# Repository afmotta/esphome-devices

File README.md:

# esphome-devices

ESPHome firmware, hardware sources and configuration for a three-floor residence's home
automation: CAN-bus wall buttons and room sensors, lighting control, and multi-zone
climate control (radiant floor + fancoil, with ventilation). The whole system is
pre-live — hardware is standardized and the firmware is built, but nothing is
physically deployed yet.

## What's where

A layered monorepo: one shared infrastructure layer, two application systems on top of
it, and the PCB sources for the CAN boards.

| Directory | Layer | What it is | Rules |
|---|---|---|---|
| [`canbus/`](canbus/) | infrastructure | CAN transport: frames, heartbeats, node discovery/health, generated node firmware | [`canbus/CLAUDE.md`](canbus/CLAUDE.md) |
| [`lighting/`](lighting/) | application | Button decode → Home Assistant events, hold automations | [`lighting/CLAUDE.md`](lighting/CLAUDE.md) |
| [`climate/`](climate/) | application | Multi-zone heating/cooling/ventilation controller | [`climate/CLAUDE.md`](climate/CLAUDE.md) |
| [`hardware/`](hardware/) | PCB sources | KiCad projects (generated by script) of the CAN wall node and the CAN bridge | [`hardware/README.md`](hardware/README.md) |
| [`registry/`](registry/) | system of record | Node table, bindings, `map.json` | [`registry/README.md`](registry/README.md) |
| `devices/`, `boards/`, `packages/` | composition | Deployable entry points, board definitions, shared packages | root [`CLAUDE.md`](CLAUDE.md) |
| [`docs/`](docs/) | knowledge base | ADRs, architecture, contracts, live climate docs, `archive/` | [`docs/adr/`](docs/adr/) |

## Maintenance & Support Guide

**[afmotta.github.io/esphome-devices](https://afmotta.github.io/esphome-devices/)** —
the practical guide for keeping this system running: everyday monitoring, diagnosing
common problems, and step-by-step hardware-replacement procedures. Written for
someone who doesn't need to know the codebase — a technician, a family member, or
future-you standing next to a dead piece of hardware having scanned a QR code.
Available in [English](https://afmotta.github.io/esphome-devices/) and
[Italiano](https://afmotta.github.io/esphome-devices/it/).

## For AI assistants / developers

See [CLAUDE.md](CLAUDE.md) for the codebase map, architecture, and conventions, and
[CONTRIBUTING.md](CONTRIBUTING.md) for secrets, logging and the registry workflow.
Verify changes with `bash scripts/verification-battery.sh` (CI runs the same gates).

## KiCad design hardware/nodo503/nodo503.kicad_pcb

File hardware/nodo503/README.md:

# Nodo CAN 503 – ESP32-C6-WROOM-1 (rev C)

Nodo per la domotica CAN del fienile, da montare in scatola 503: un morsetto per 24 V e bus CAN, transceiver TJA1051T/3, 6 ingressi pulsante, porta Qwiic (I²C) e modulo **ESP32-C6-WROOM-1-N8** (LCSC C5366877) con Wi-Fi per ESPHome e aggiornamenti OTA. È pensato per il montaggio completo da JLCPCB, con tutti i componenti su un solo lato.

- **Dimensioni:** 55 × 33,5 mm (entro i 56 × 41 mm della CANBed RP2040), 2 strati, spessore 1,6 mm, rame 1 oz
- **Fissaggio:** 2 fori M2,5 non metallizzati (Ø 2,7 mm) in diagonale, in alto a destra e in basso a sinistra, con il centro a 3 mm dai bordi: interasse **49 × 27,5 mm**. Entro 2,8 mm dal centro di ogni foro non ci sono componenti, piste né via, così la testa della vite (fino a Ø 5 mm) appoggia solo su piano di massa coperto da solder mask. L'angolo dell'antenna (in alto a sinistra) resta senza vite: nel case ci sono due appoggi sotto gli angoli senza vite (vedi [case/README.md](case/README.md)).
- **Progetto:** KiCad 7 (si apre anche in KiCad 8/9)
- **Simbolo e footprint del modulo:** dalla libreria ufficiale [espressif/kicad-libraries](https://github.com/espressif/kicad-libraries), licenza CC-BY-SA 4.0. Il footprint comprende anche l'area dell'antenna senza rame.

> Questa è la scheda `hardware/nodo503/`. Per la panoramica di `hardware/` e per la pipeline condivisa vedi [../README.md](../README.md); la seconda scheda, il **bridge CAN** a due canali, è in [../bridge/README.md](../bridge/README.md).

## Contenuto della cartella

Percorsi relativi a `hardware/nodo503/`.

| Percorso | Cosa contiene |
|---|---|
| `nodo503.kicad_pro / .kicad_sch / .kicad_pcb` | Progetto KiCad 7 completo (si apre con KiCad 7, 8 o 9) |
| `nodo503.kicad_sym`, `nodo503.pretty/` | Simbolo e footprint del modulo ESP32-C6-WROOM-1 (libreria di progetto) |
| `out/gerber_JLCPCB.zip` | Gerber + foratura, da caricare così com'è su JLCPCB |
| `out/BOM.csv`, `CPL_JLCPCB.csv` | Distinta e piazzamento per il montaggio completo (SMD + THT) |
| `out/BOM_SMD.csv`, `CPL_SMD.csv` | Distinta e piazzamento solo SMD |
| `out/nodo503_schema.pdf`, `anteprima_lato_*.png` | Schema elettrico e anteprime rame + serigrafia |
| `jlc_library.json` | Libreria JLCPCB (Basic / Preferred / Extended) di ogni codice LCSC |
| `*.py`, `*.sh` | Script che generano schema, PCB, sbroglio e file di produzione (vedi [../docs/pipeline.md](../docs/pipeline.md)) |
| `firmware/nodo503.yaml` | Firmware ESPHome di bring-up (Wi-Fi, API, OTA, 6 pulsanti) |
| [`case/`](case/README.md) | Involucro stampato in 3D (fondo + coperchio a scatto): generatore `gen_case.py`, STL e anteprima |
| [`../docs/decisioni.md`](../docs/decisioni.md) | Storia del progetto e motivazioni delle scelte |
| [`../docs/pipeline.md`](../docs/pipeline.md) | Come rigenerare tutto, struttura degli script, problemi noti |
| [`../CLAUDE.md`](../CLAUDE.md) | Regole per le sessioni di Claude Code su `hardware/` |
| [`../tools/setup.sh`](../tools/setup.sh) | Installa KiCad 7, Freerouting 1.9.0 e le dipendenze Python |

Per rigenerare i file di produzione dopo una modifica: `sudo hardware/tools/setup.sh` (una volta, dalla radice del repo), poi da questa cartella `./route.sh` se cambiano piazzamento o collegamenti, `./build_pcb.sh` se basta lo sbroglio salvato, e infine `./export.sh`.

## Circuito

- **Ingresso 24 V:** PTC da 0,5 A (F1), diodo B5819W contro l'inversione di polarità (D1, 1 A: basta per il PTC da 0,5 A), TVS SMBJ26CA (D2), elettrolitico da 10 µF 50 V e MLCC da 10 µF 50 V in ingresso.
- **5 V:** MORNSUN K7805-500R3 (U1), switching con pin compatibili 7805. Alimenta il TJA1051.
- **3,3 V:** LDO AP2112K-3.3 (U4, 600 mA). Due diodi B5819W (D3, D5) in "OR" lo alimentano dai 5 V del K7805 oppure dai 5 V del pettine di programmazione: il modulo si programma anche senza i 24 V, e la tensione dell'USB non risale verso il K7805.
- **CAN:** TJA1051T/3 con VIO a 3,3 V (nessun partitore sulle linee logiche), pin S a GND, protezione ESD NUP2105L sulle linee del bus. **Nessuna terminazione da 120 Ω** a bordo: il bus va terminato agli estremi della linea.
- **Microcontrollore:** modulo ESP32-C6-WROOM-1-N8 (flash 8 MB, antenna su PCB), con l'antenna a filo del bordo superiore della scheda. Rete RC su EN (10 kΩ + 1 µF) e pull-up da 10 kΩ su GPIO8, come raccomanda Espressif.
- **Ingressi pulsante:** per ciascuno pull-up da 3,3 kΩ a 3,3 V (circa 1 mA nel contatto chiuso, per tenere puliti i contatti in argento dei pulsanti da rete), resistenza in serie da 1 kΩ e condensatore da 100 nF verso GND (τ ≈ 100 µs). Il pulsante chiude verso GND (logica attiva bassa). Componenti 0402 in tre colonne per lato: pulsanti 1–3 a sinistra del modulo, 4–6 a destra.

## Pinout

| Funzione | GPIO | Pin modulo WROOM |
|---|---|---|
| CAN TXD | GPIO23 | 21 |
| CAN RXD | GPIO22 | 20 |
| Pulsante 1 | GPIO7 | 7 |
| Pulsante 2 | GPIO0 | 8 |
| Pulsante 3 | GPIO1 | 9 |
| Pulsante 4 | GPIO20 | 18 |
| Pulsante 5 | GPIO19 | 17 |
| Pulsante 6 | GPIO18 | 16 |
| Qwiic SDA | GPIO3 | 26 |
| Qwiic SCL | GPIO2 | 27 |
| USB D− / D+ (programmazione) | GPIO12 / GPIO13 | 13 / 14 |
| BOOT (pin 5 di J5) | GPIO9 | 15 |
| Pull-up di boot | GPIO8 | 10 |
| Liberi | GPIO4, 5, 6, 10, 11, 15, 16, 17, 21 | – |

Rispetto alla versione 48 × 44 mm i GPIO di pulsanti, Qwiic e CAN sono cambiati: i pulsanti 1–3 usano i pin del lato sinistro del modulo, i pulsanti 4–6 quelli del lato destro, così le piste non si incrociano. GPIO4, GPIO5, GPIO8, GPIO9 e GPIO15 sono pin di strapping: se in futuro ne usi uno, tieni conto del livello che deve avere all'avvio.

## Connettori

- **J1 BUS:** morsetto estraibile ad angolo a 4 poli, passo 3,5 mm, sul bordo destro. Sulla scheda c'è la presa (Kefa KF2EDGR-3.5-4P), a filo del bordo; i fili vanno nella spina a vite (KF2EDGK-3.5-4P), che si innesta di lato da destra, quindi i fili escono paralleli alla scheda come prima. La spina sporge di circa 1 cm oltre il bordo: lascia lo spazio nel case. Dall'alto in basso: 24V – GND – CAN-H – CAN-L.
- **Catena del bus:** il morsetto del bus è uno solo, quindi il cavo che arriva e quello che riparte verso il nodo successivo vanno nello stesso polo della spina (due fili per polo, meglio con un puntale doppio; la spina accetta fino a 1,5 mm² in tutto). Il collegamento tra i due cavi lo fa la spina stessa: sfilandola stacchi la scheda senza interrompere il bus e l'alimentazione degli altri nodi.
- **J3 e J4 PULSANTI:** due connettori JST PH a 4 poli (passo 2 mm, B4B-PH-K-S verticale) sul bordo inferiore, sotto il modulo. **J3** (a sinistra): pulsanti 1, 2, 3, GND da sinistra. **J4** (a destra): pulsanti 4, 5, 6, GND. I connettori sono ruotati di 180°: il pin 1 (tacca quadrata) è a destra ed è il GND, il pin 4 è il pulsante 1 (o 4). Nella maggior parte dei casi basta J3; J4 serve solo per i nodi con più di 3 pulsanti. Il cavo si innesta dall'alto (fili perpendicolari alla scheda) e si sfila per staccare la scheda. Alto 6 mm, 8 mm con il cavo innestato: il componente più alto della scheda resta il K7805.
- **Cavi dei pulsanti:** un cavo a 4 fili per gruppo, con il connettore JST PHR-4 e i contatti SPH-002T-P0.5S (filo da AWG 30 a AWG 24, cioè fino a 0,2 mm²). Il modo più semplice è comprare cavetti PH 2,0 a 4 poli già crimpati, con fili **AWG 24** lunghi 10–15 cm. Il connettore non si salda: si ordina a parte, come prima la spina. La corrente è di circa 1 mA, quindi la sezione conta solo per la meccanica.
- **Collegamento ai frutti:** i pulsanti Vimar Linea hanno morsetti a vite pensati per fili da rete. Metti un **puntale da 0,25 mm²** su ogni filo (oppure ripiega il filo spelato) perché la vite stringa bene. Il GND di ogni cavo va al comune dei 3 frutti del suo gruppo.
- **Montaggio nella scatola:** il JST PH resta innestato per attrito, senza dente di blocco. Lascia un po' di lasco ai cavi quando spingi i frutti nella 503, ed etichetta i due cavi (1–3 e 4–6): hanno lo stesso connettore e si possono scambiare. Nelle scatole dei pulsanti non ci sono conduttori a 230 V; se un giorno ci fossero, i fili sottili dei cavetti PH (isolamento da 300 V) non andrebbero bene così.
- **J2 Qwiic:** JST SH a 4 pin, passo 1 mm, sul bordo superiore a destra con l'imbocco verso l'alto. GND, 3,3 V, SDA, SCL. **Nessun pull-up I²C sulla scheda:** li forniscono il QwiicBus e le schede dei sensori.
- **J5 PROG:** pettine 1×6 a passo 2,54 mm, orizzontale sul bordo inferiore a destra, da non montare (fori passanti). Pin da sinistra: 5V, D−, D+, GND, BOOT, GND (serigrafati sopra i fori). I pin 1–4 vanno al cavo USB (USB nativo del C6). Un ponticello sui pin 5–6 porta GPIO9 a massa e fa partire il modulo in modalità download.

Nessuna terminazione da 120 Ω sulla scheda: il bus va terminato agli estremi della linea.

## Prima programmazione

1. Collega un cavo USB al pettine J5: rosso al 5V, bianco a D−, verde a D+, nero a GND. Puoi saldare un pettine maschio 1×6, oppure infilarne uno nei fori e tenerlo premuto mentre programmi.
2. Con il flash vuoto il modulo di solito entra da solo in modalità download. Se non succede, o se un firmware difettoso ha bloccato l'USB:
   - metti un ponticello sui pin 5–6 di J5 (BOOT–GND);
   - collega l'USB, oppure accendi la scheda;
   - programma, poi **togli il ponticello**. Se lo lasci, il modulo resta in modalità download a ogni riavvio e il firmware non parte.
3. Programma con ESPHome (o esptool) via USB. Dal flash successivo puoi usare l'OTA via Wi-Fi.

## Da verificare prima dell'ordine

1. **Codici LCSC e magazzino.** Tutti i componenti montati hanno un codice LCSC. Al caricamento della BOM controlla la disponibilità, soprattutto di J2 (vedi sotto).
2. **Rotazioni nel file CPL.** Controllale nell'anteprima di assemblaggio JLCPCB, soprattutto per il modulo U3 (l'antenna deve stare a filo del bordo superiore, sopra l'area senza rame), U2, U4 (ruotato di 180°), J2 (ruotato di 180°, imbocco verso l'alto), J1 (ruotato di 90°, imbocco della spina verso il bordo destro), J3 e J4 (la tacca del connettore deve coincidere con quella del footprint), i diodi e C1.
3. **Via nel pad di massa del modulo.** Il pad di massa sotto il WROOM è una griglia 3×3 con 5 via verso la massa sul retro. Su JLCPCB conviene chiedere che le via siano tappate ("via-in-pad" o "epoxy filled"), così lo stagno non cola nei fori. Se non lo fai, di solito funziona comunque.
4. **Piste sotto il modulo.** La pista +3V3 tra i due lati del modulo e le piste USB verso il pettine di programmazione passano sotto il modulo, lontano dall'antenna (sullo strato superiore e sul retro). È ammesso, ma lascia meno piano di massa sotto il modulo.
5. **Fori di J1.** Il footprint Phoenix MC ha fori da 1,2 mm. Il datasheet Kefa non è consultabile da qui: confronta il diametro con il footprint EasyEDA di C441173 (pagina del componente su LCSC o JLCPCB) prima di ordinare. J3 e J4 usano il footprint KiCad del JST PH originale.

## Montaggio

- **Montaggio completo:** carica `BOM.csv` e `CPL_JLCPCB.csv`. JLCPCB monta anche i THT (K7805-500R3, J1, J3 e J4) a onda o a mano. Non resta nulla da saldare, J5 resta senza componente. La spina KF2EDGK-3.5-4P (J1) e i cavi PH per J3/J4 si ordinano a parte.
- **Solo SMD:** carica `BOM_SMD.csv` e `CPL_SMD.csv`. Il K7805, J1, J3 e J4 restano da saldare a mano.

## Firmware ESPHome

Il file `firmware/nodo503.yaml` è una prima versione per collegare il nodo a Home Assistant: Wi-Fi, API cifrata, OTA, 6 pulsanti (GPIO7/0/1 e 20/19/18) e segnale Wi-Fi. CAN e I²C sono lasciati commentati in fondo al file.

1. Copia `firmware/secrets.yaml.example` in `firmware/secrets.yaml` (ignorato da git) e compila SSID, password e chiavi.
2. Dalla cartella `firmware/` esegui `esphome run nodo503.yaml` (o carica il file nella dashboard ESPHome). Il primo flash è via USB su J5, dopo si può usare l'OTA.
3. Home Assistant scopre il dispositivo da solo (Impostazioni → Dispositivi → ESPHome).

Se J4 non è collegato, i pulsanti 4–6 restano semplicemente spenti.

## Firmware per la rete CAN

Il firmware di produzione non è in questa cartella: il profilo `buttons-c6` del registry usa la scheda [`boards/esp32-c6-nodo503.yaml`](../../boards/esp32-c6-nodo503.yaml) (ADR-0025, vedi [`docs/adr/0025-esp32-c6-node-and-bridge-boards.md`](../../docs/adr/0025-esp32-c6-node-and-bridge-boards.md)); i file dei nodi si generano da `registry/nodes.csv` con `canbus/tools/generate_nodes.py`. Il file `firmware/nodo503.yaml` (vedi sopra) è solo il bring-up Wi-Fi/Home Assistant.

## BOM e librerie JLCPCB (aggiornata il 2026-10-14)

Tutti i componenti hanno un codice LCSC e sono pensati per il montaggio completo da JLCPCB, compresi i THT (J1, J3, J4 e K7805 U1, saldati da JLCPCB a onda o a mano). La colonna **Libreria JLCPCB** della BOM indica Basic / Preferred / Extended; l'elenco usato è in `nodo503/jlc_library.json`.

- **Non montati:** solo **J5** (pettine di programmazione, DNP). Per programmare si usa un pettine inserito al momento o saldato.
- **C2** è passato da 2,2 µF a **10 µF 50 V 1206** (C13585, Basic): più capacità in ingresso al K7805 e un componente Extended in meno.
- **C1:** Honor Elec RVT1H100M0505 (C86603, Extended), 10 µF 50 V, 5 × 5,4 mm, 105 °C. Dalla ricerca risultavano circa 6 000 pezzi su LCSC: verificalo al caricamento della BOM.
- **D1:** B5819W (C8598, Basic), lo stesso diodo di D3 e D5: al posto dello SS34 in SMA.
- **J1:** presa Kefa KF2EDGR-3.5-4P (C441173, Extended, ad angolo, 10 A 300 V, saldatura a onda, PCBA Economic e Standard), footprint Phoenix MC 1,5/4-G-3,5 orizzontale, fronte della presa a filo del bordo destro. A magazzino LCSC 7 295 pezzi il 2026-10-18. Prima dell'ordine verifica nell'anteprima JLCPCB che l'imbocco della spina sia verso il bordo.
- **Spina per J1 da ordinare a parte:** Kefa KF2EDGK-3.5-4P (LCSC C440849, 12 196 pezzi il 2026-10-18), vite M2, filo fino a 1,5 mm².
- **J3 e J4:** JST B4B-PH-K-S(LF)(SN) originale (C131334, Extended, saldatura a onda), lo stesso codice per i due connettori. Dalla ricerca del 2026-10-19 risultavano circa 95 000 pezzi su LCSC: verificalo al caricamento della BOM.
- **Cavi per J3/J4 da ordinare a parte:** cavetti PH 2,0 a 4 poli già crimpati (fili AWG 24), oppure connettori JST PHR-4 con contatti SPH-002T-P0.5S da crimpare. Non sono nella BOM di montaggio perché non si saldano.
- **CPL:** per i THT la posizione è il centro dei pin (non il pin 1). Controlla nell'anteprima di assemblaggio le rotazioni dei morsetti e del K7805.
- **J2 (C160404) ha pochissimi pezzi a magazzino.** Alternative compatibili Qwiic (Extended, da confrontare con il footprint): ZX-SH1.0-4PWT C7430446, HC-1.0-4PWT C2845363, BX-SH1.0-4PWT C18077910.
- Le pagine JLCPCB dei componenti Preferred mostrano solo "Extended": al caricamento della BOM verifica che abbiano il badge "Preferred".

## Storia e decisioni

Esiste anche una variante con un unico morsetto estraibile Kefa a 7 poli per i pulsanti (scheda 55 × 37 mm, spina a vite e cordina da 0,5 mm²): è nel branch `variante/kefa` del repo archiviato `afmotta/can-bus-node`, con i suoi file di produzione. Non è stata importata in questo monorepo.

La storia del progetto (rev A con XIAO, rev B con MINI-1, revisione di un esperto, passaggio a 56 × 41 mm e poi a 55 × 33,5 mm, scelta dei connettori) e il motivo di ogni scelta sono in [../docs/decisioni.md](../docs/decisioni.md).

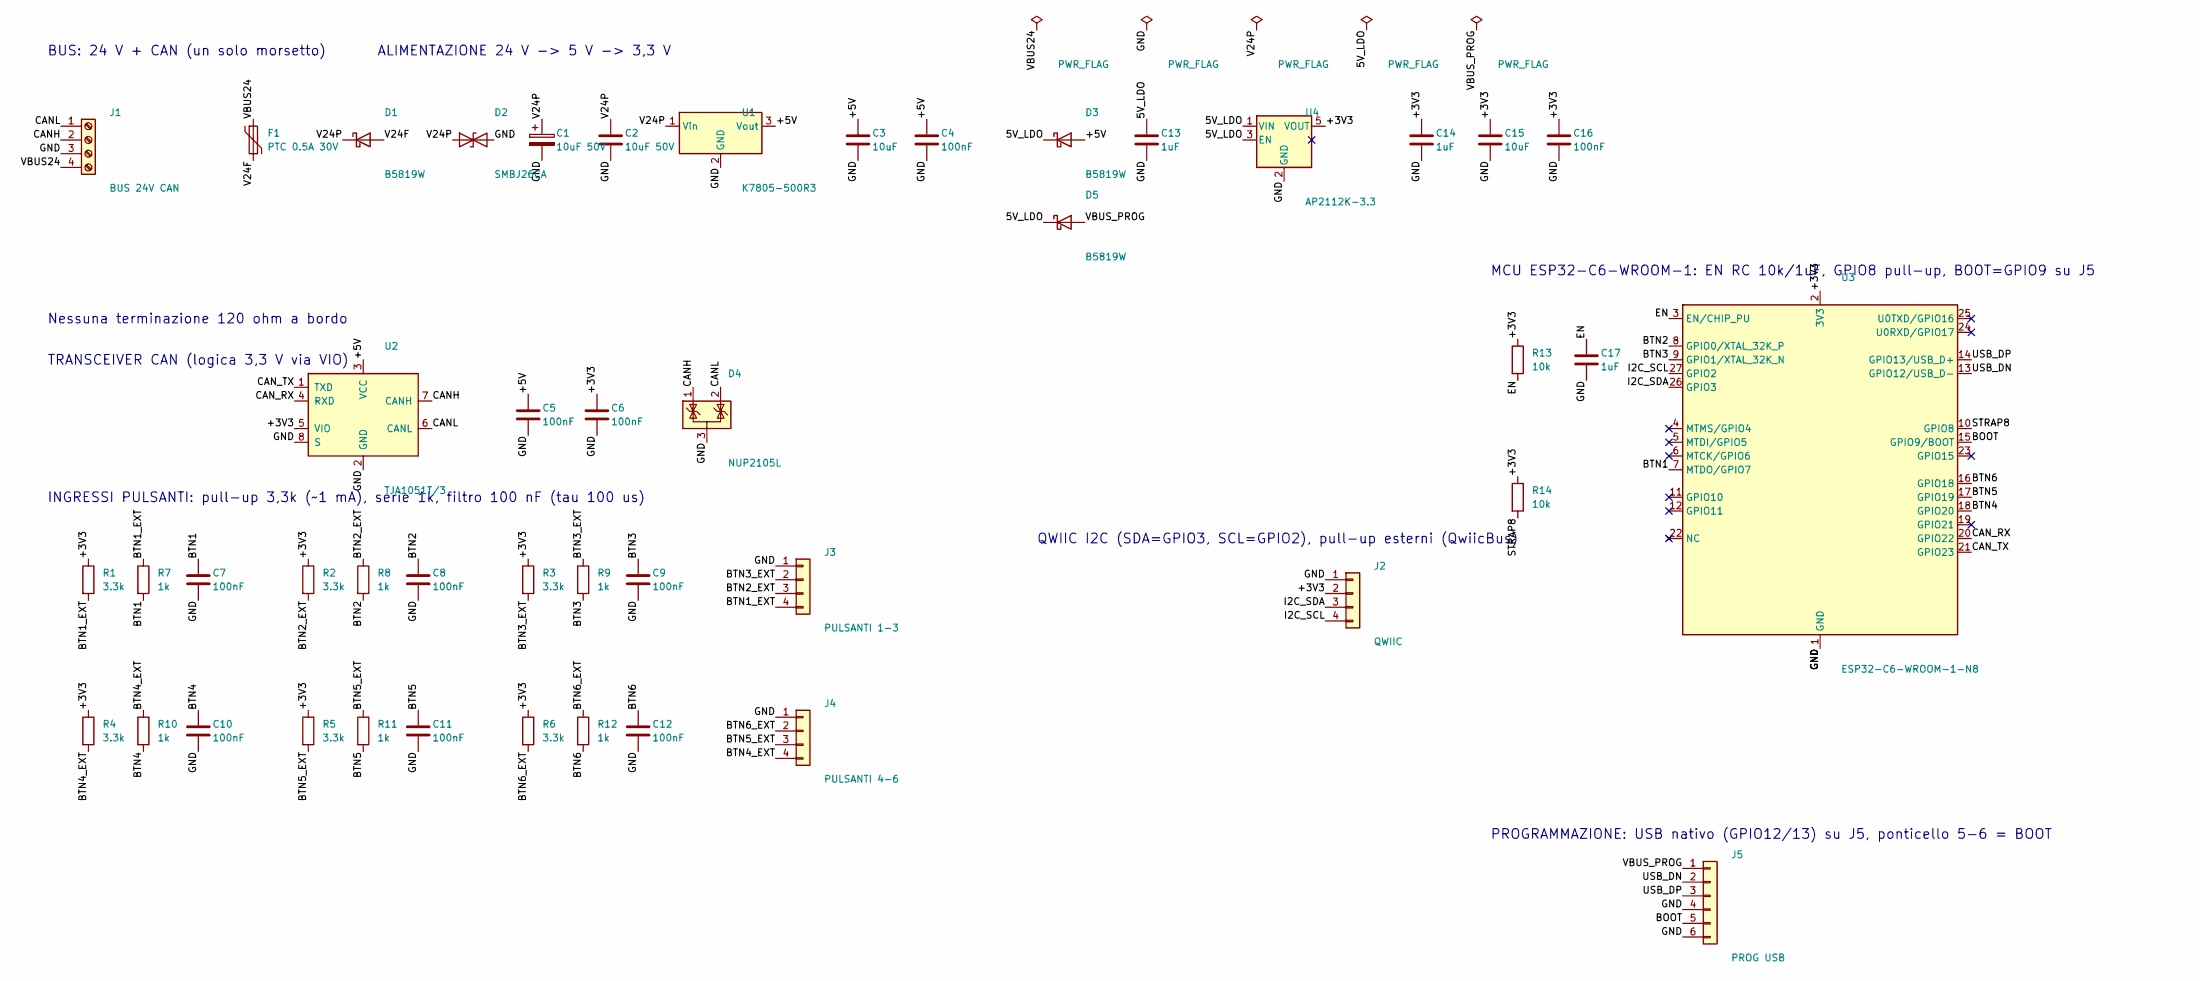
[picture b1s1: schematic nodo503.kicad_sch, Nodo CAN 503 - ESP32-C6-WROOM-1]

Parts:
C1: 10uF 50V; CP_Elec_5x5.4; MPN Honor Elec RVT1H100M0505, elettrolitico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; LCSC C86603
C2: 10uF 50V; C_1206_3216Metric; MPN MLCC 10 uF 50 V X5R 1206 (Samsung CL31A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; LCSC C13585
C3: 10uF; C_0805_2012Metric; MPN MLCC 10 uF 25 V 0805; LCSC C15850
C4, C5, C6, C16: 100nF; C_0603_1608Metric; MPN MLCC 100 nF 50 V 0603; LCSC C14663
C7, C8, C9, C10, C11, C12: 100nF; C_0402_1005Metric; MPN MLCC 100 nF 0402; LCSC C1525
C13, C14: 1uF; C_0603_1608Metric; MPN MLCC 1 uF 50 V X5R 0603 (Samsung CL10A1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; LCSC C15849
C15: 10uF; C_0603_1608Metric; MPN MLCC 10 uF 10 V X5R 0603 (Samsung CL10A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; LCSC C19702
C17: 1uF; C_0402_1005Metric; MPN MLCC 1 uF 25 V X5R 0402 (Samsung CL05A1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; LCSC C52923
D1: B5819W; D_SOD-123; MPN B5819W (40 V 1 A) - protezione inversio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; LCSC C8598
D2: SMBJ26CA; D_SMB; MPN SMBJ26CA TVS bidirezionale 26 V, SMB (h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; LCSC C19077581
D3: B5819W; D_SOD-123; MPN B5819W - OR alimentazione LDO (da 5 V b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; LCSC C8598
D4: NUP2105L; SOT-23; MPN onsemi NUP2105LT1G - ESD bus CAN 24 V; LCSC C14486
D5: B5819W; D_SOD-123; MPN B5819W - OR alimentazione LDO (da USB d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; LCSC C8598
F1: PTC 0.5A 30V; Fuse_1812_4532Metric; MPN PTC 1812 RUILON SMD1812P050TF/30 (0,5 A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; LCSC C12559
J1: BUS 24V CAN; PhoenixContact_MC_1,5_4-G-3.5_1x04_P3.50mm_Horizontal; MPN Presa per morsetto estraibile ad angolo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; LCSC C441173
J2: QWIIC; JST_SH_SM04B-SRSS-TB_1x04-1MP_P1.00mm_Horizontal; MPN JST SM04B-SRSS-TB(LF)(SN) (Qwiic, SH 1 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; LCSC C160404
J3: PULSANTI 1-3; JST_PH_B4B-PH-K_1x04_P2.00mm_Vertical; MPN JST B4B-PH-K-S(LF)(SN), PH 2 mm 4 poli 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; LCSC C131334
J4: PULSANTI 4-6; JST_PH_B4B-PH-K_1x04_P2.00mm_Vertical; MPN JST B4B-PH-K-S(LF)(SN), PH 2 mm 4 poli 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; LCSC C131334
J5: PROG USB; PinHeader_1x06_P2.54mm_Vertical; MPN Pettine 1x6 2,54 mm (non montato): 5V, 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
R1, R2, R3, R4, R5, R6: 3.3k; R_0402_1005Metric; MPN 3.3 kOhm 1% 0402 (UNI-ROYAL 0402WGF3301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; LCSC C25890
R7, R8, R9, R10, R11, R12: 1k; R_0402_1005Metric; MPN 1 kOhm 1% 0402; LCSC C11702
R13: 10k; R_0402_1005Metric; MPN 10 kOhm 1% 0402; LCSC C25744
R14: 10k; R_0402_1005Metric; MPN 10 kOhm 1% 0402 (GPIO8 alto al boot); LCSC C25744
U1: K7805-500R3; Converter_DCDC_TRACO_TSR-1_THT; MPN MORNSUN K7805-500R3 (6,5-36 V -> 5 V 0,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; LCSC C86735
U2: TJA1051T/3; SOIC-8_3.9x4.9mm_P1.27mm; MPN NXP TJA1051T/3/1J; LCSC C38695
U3: ESP32-C6-WROOM-1-N8; ESP32-C6-WROOM-1; MPN Espressif ESP32-C6-WROOM-1-N8; LCSC C5366877
U4: AP2112K-3.3; SOT-23-5; MPN Diodes AP2112K-3.3TRG1 (LDO 600 mA); LCSC C51118

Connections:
5V_LDO: C13.1, D3.1 (K), D5.1 (K), U4.1 (VIN), U4.3 (EN)
+3V3: C6.1, C14.1, C15.1, C16.1, J2.2, R1.1, R2.1, R3.1, R4.1, R5.1, R6.1, R13.1, R14.1, U2.5 (VIO), U3.2 (3V3), U4.5 (VOUT)
+5V: C3.1, C4.1, C5.1, D3.2 (A), U1.3 (Vout), U2.3 (VCC)
BOOT: J5.5, U3.15 (GPIO9/BOOT)
BTN1: C7.1, R7.2, U3.7 (MTDO/GPIO7)
BTN1_EXT: J3.4, R1.2, R7.1
BTN2: C8.1, R8.2, U3.8 (GPIO0/XTAL_32K_P)
BTN2_EXT: J3.3, R2.2, R8.1
BTN3: C9.1, R9.2, U3.9 (GPIO1/XTAL_32K_N)
BTN3_EXT: J3.2, R3.2, R9.1
BTN4: C10.1, R10.2, U3.18 (GPIO20)
BTN4_EXT: J4.4, R4.2, R10.1
BTN5: C11.1, R11.2, U3.17 (GPIO19)
BTN5_EXT: J4.3, R5.2, R11.1
BTN6: C12.1, R12.2, U3.16 (GPIO18)
BTN6_EXT: J4.2, R6.2, R12.1
CANH: D4.1 (K), J1.2, U2.7 (CANH)
CANL: D4.2 (K), J1.1, U2.6 (CANL)
CAN_RX: U2.4 (RXD), U3.20 (GPIO22)
CAN_TX: U2.1 (TXD), U3.21 (GPIO23)
EN: C17.1, R13.2, U3.3 (EN/CHIP_PU)
GND: C1.2, C2.2, C3.2, C4.2, C5.2, C6.2, C7.2, C8.2, C9.2, C10.2, C11.2, C12.2, C13.2, C14.2, C15.2, C16.2, C17.2, D2.2 (A2), D4.3 (A), J1.3, J2.1, J3.1, J4.1, J5.4, J5.6, U1.2 (GND), U2.2 (GND), U2.8 (S), U3.1 (GND), U3.28 (GND), U3.29 (GND), U4.2 (GND)
I2C_SCL: J2.4, U3.27 (GPIO2)
I2C_SDA: J2.3, U3.26 (GPIO3)
STRAP8: R14.2, U3.10 (GPIO8)
USB_DN: J5.2, U3.13 (GPIO12/USB_D-)
USB_DP: J5.3, U3.14 (GPIO13/USB_D+)
V24F: D1.2 (A), F1.2
V24P: C1.1, C2.1, D1.1 (K), D2.1 (A1), U1.1 (Vin)
VBUS24: F1.1, J1.4
VBUS_PROG: D5.2 (A), J5.1

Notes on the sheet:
BUS: 24 V + CAN (un solo morsetto)
ALIMENTAZIONE 24 V -> 5 V -> 3,3 V
Nessuna terminazione 120 ohm a bordo
TRANSCEIVER CAN (logica 3,3 V via VIO)
MCU ESP32-C6-WROOM-1: EN RC 10k/1uF, GPIO8 pull-up, BOOT=GPIO9 su J5
PROGRAMMAZIONE: USB nativo (GPIO12/13) su J5, ponticello 5-6 = BOOT
QWIIC I2C (SDA=GPIO3, SCL=GPIO2), pull-up esterni (QwiicBus)
INGRESSI PULSANTI: pull-up 3,3k (~1 mA), serie 1k, filtro 100 nF (tau 100 us)

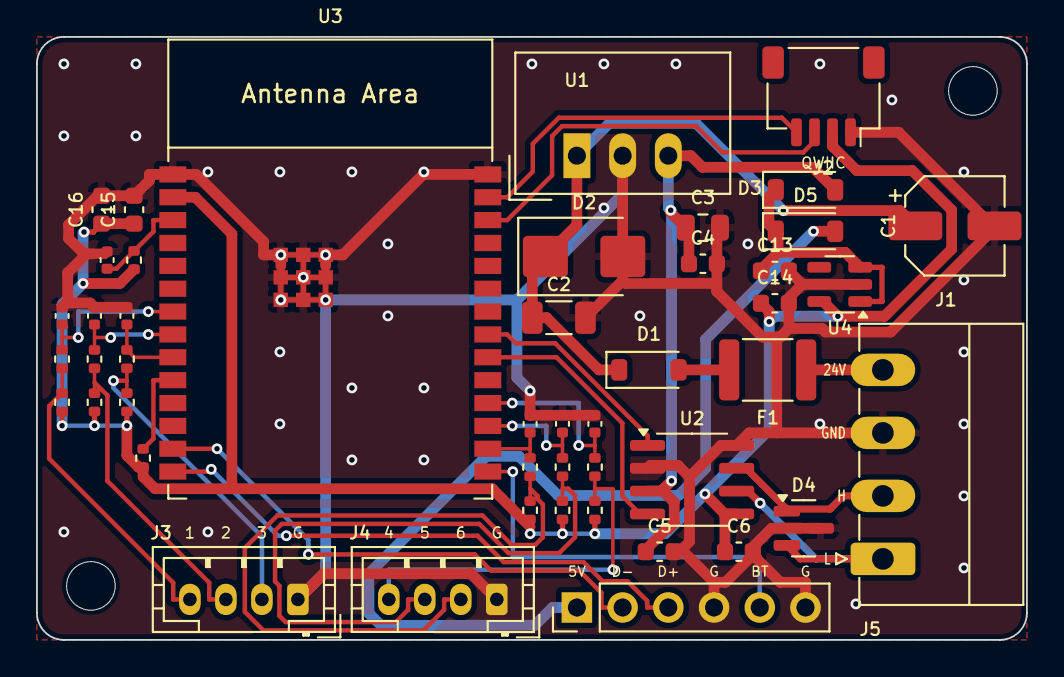
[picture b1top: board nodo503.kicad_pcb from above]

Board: 2 copper layers, 55.0 x 33.5 mm, 48 parts (0 on the bottom side), 31 nets.

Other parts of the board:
H1, H2: M2.5; MountingHole_2.7mm_M2.5

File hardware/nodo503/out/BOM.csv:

Comment,Designator,Footprint,Quantita,Descrizione / MPN,LCSC,Libreria JLCPCB
10uF 50V,C1,CP_Elec_5x5.4,1,"Honor Elec RVT1H100M0505, elettrolitico SMD 10 uF 50 V, D5x5.4 mm, 105 C",C86603,Extended
10uF 50V,C2,C_1206_3216Metric,1,MLCC 10 uF 50 V X5R 1206 (Samsung CL31A106KBHNNNE),C13585,Basic
10uF,C3,C_0805_2012Metric,1,MLCC 10 uF 25 V 0805,C15850,Basic
100nF,"C4,C5,C6,C16",C_0603_1608Metric,4,MLCC 100 nF 50 V 0603,C14663,Basic
100nF,"C7,C8,C9,C10,C11,C12",C_0402_1005Metric,6,MLCC 100 nF 0402,C1525,Basic
1uF,"C13,C14",C_0603_1608Metric,2,MLCC 1 uF 50 V X5R 0603 (Samsung CL10A105KB8NNNC),C15849,Basic
10uF,C15,C_0603_1608Metric,1,"MLCC 10 uF 10 V X5R 0603 (Samsung CL10A106KP8NNNC), vicino al modulo",C19702,Basic
1uF,C17,C_0402_1005Metric,1,MLCC 1 uF 25 V X5R 0402 (Samsung CL05A105KA5NQNC) - RC su EN,C52923,Basic
B5819W,D1,D_SOD-123,1,B5819W (40 V 1 A) - protezione inversione polarita',C8598,Basic
SMBJ26CA,D2,D_SMB,1,"SMBJ26CA TVS bidirezionale 26 V, SMB (hongjiacheng)",C19077581,Preferred
B5819W,D3,D_SOD-123,1,B5819W - OR alimentazione LDO (da 5 V bus),C8598,Basic
NUP2105L,D4,SOT-23,1,onsemi NUP2105LT1G - ESD bus CAN 24 V,C14486,Extended
B5819W,D5,D_SOD-123,1,B5819W - OR alimentazione LDO (da USB di programmazione),C8598,Basic
PTC 0.5A 30V,F1,Fuse_1812_4532Metric,1,"PTC 1812 RUILON SMD1812P050TF/30 (0,5 A hold, 30 V)",C12559,Extended
BUS 24V CAN,J1,"PhoenixContact_MC_1,5_4-G-3.5_1x04_P3.50mm_Horizontal",1,"Presa per morsetto estraibile ad angolo 4 poli passo 3,5 mm, Kefa KF2EDGR-3.5-4P (THT); spina KF2EDGK-3.5-4P C440849 da ordinare a parte",C441173,Extended - THT (saldatura a onda/manuale JLCPCB)
QWIIC,J2,JST_SH_SM04B-SRSS-TB_1x04-1MP_P1.00mm_Horizontal,1,"JST SM04B-SRSS-TB(LF)(SN) (Qwiic, SH 1 mm, orizzontale)",C160404,Extended
PULSANTI 1-3,J3,JST_PH_B4B-PH-K_1x04_P2.00mm_Vertical,1,"JST B4B-PH-K-S(LF)(SN), PH 2 mm 4 poli verticale (THT); cavo con terminali SPH-002T-P0.5S da crimpare o precrimpato",C131334,Extended - THT (saldatura a onda/manuale JLCPCB)
PULSANTI 4-6,J4,JST_PH_B4B-PH-K_1x04_P2.00mm_Vertical,1,"JST B4B-PH-K-S(LF)(SN), PH 2 mm 4 poli verticale (THT); cavo con terminali SPH-002T-P0.5S da crimpare o precrimpato",C131334,Extended - THT (saldatura a onda/manuale JLCPCB)
PROG USB,J5,PinHeader_1x06_P2.54mm_Vertical,1,"Pettine 1x6 2,54 mm (non montato): 5V, D-, D+, GND, BOOT, GND - ponticello 5-6 = download",,non montato (DNP)
3.3k,"R1,R2,R3,R4,R5,R6",R_0402_1005Metric,6,3.3 kOhm 1% 0402 (UNI-ROYAL 0402WGF3301TCE),C25890,Basic
1k,"R7,R8,R9,R10,R11,R12",R_0402_1005Metric,6,1 kOhm 1% 0402,C11702,Basic
10k,R13,R_0402_1005Metric,1,10 kOhm 1% 0402,C25744,Basic
10k,R14,R_0402_1005Metric,1,10 kOhm 1% 0402 (GPIO8 alto al boot),C25744,Basic
K7805-500R3,U1,Converter_DCDC_TRACO_TSR-1_THT,1,"MORNSUN K7805-500R3 (6,5-36 V -> 5 V 0,5 A, SIP-3, pin 78xx)",C86735,Extended - THT (saldatura a onda/manuale JLCPCB)
TJA1051T/3,U2,SOIC-8_3.9x4.9mm_P1.27mm,1,NXP TJA1051T/3/1J,C38695,Extended
ESP32-C6-WROOM-1-N8,U3,ESP32-C6-WROOM-1,1,Espressif ESP32-C6-WROOM-1-N8,C5366877,Extended
AP2112K-3.3,U4,SOT-23-5,1,Diodes AP2112K-3.3TRG1 (LDO 600 mA),C51118,Extended
KF2EDGK-3.5-4P,P1,"Spina 3,5 mm 4 poli (per J1)",1,"Spina per morsetto estraibile 4 poli passo 3,5 mm, Kefa KF2EDGK-3.5-4P (non montata: spedita con i PCB)",C440849,"classe da verificare - solo BOM, non montata, spedita con i PCB"

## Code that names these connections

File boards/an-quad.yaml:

# =============================================================================
# an-quad.yaml — QuinLED-An-Quad board hardware
# =============================================================================
# Generic board package for the QuinLED-An-Quad: a classic-ESP32, WiFi-only,
# 4-channel analog (PWM) LED controller. Unlike the An-Penta-Plus it has NO
# Ethernet PHY, so WiFi is the only network and needs no `network: priority:`
# arbitration — a board with both interfaces (the An-Penta-Plus) declares
# ethernet+wifi together and lists both under network: priority: (ADR-0022),
# whereas the An-Quad, with one interface, just declares wifi inline here. This
# file owns only fixed board hardware and the esp32/wifi/api/ota scaffolding. How
# the four output channels are grouped into light entities (monochrome / CCT /
# RGB / RGBW) and whether the two spare header GPIOs carry anything (a CAN
# transceiver, in the actuator deployment) are application composition and belong
# in the entry point, not here (AD-4: entry-point composition, not board concerns).
#
# Hardware reference (quinled.info An-Quad pinout + its ESPHome sample config):
#   LED ch1  GPIO16   LED ch2  GPIO17   LED ch3  GPIO5*   LED ch4  GPIO19
#   Onboard DS18B20 temperature sensor  GPIO18   (left UNCLAIMED; app policy)
#   Two spare GPIOs on the pin header   GPIO22 / GPIO23  (aux_gpio_1/aux_gpio_2)
#   * GPIO5 is an ESP32 strapping pin (boot log / SDIO timing); the board is
#     designed around driving an LED channel on it, so its LEDC output sets
#     ignore_strapping_warning below (same discipline as the An-Penta's GPIO12/2).
#
#   NOTE: the two spare-header GPIOs (aux_gpio_1/aux_gpio_2) are wired to the
#   external CAN transceiver in the ADR-0020/ADR-0021 actuator deployment (see the
#   entry point devices/an-quad-1.yaml). The An-Quad, unlike the An-Penta-Plus, has
#   no QWIIC/I2C header — these are its plain expansion-header GPIOs, confirmed from
#   the An-Quad schematic (GPIO22 = tx, GPIO23 = rx). Neither is a strapping pin, so
#   the tx/rx assignment is free; flip it if the transceiver is wired the other way.
# =============================================================================

substitutions:
  # Placeholder default only. Every entry point overrides device_name (and
  # friendly_name), and that override wins for the resolved esphome.name. It is
  # kept here so the ${device_name} references in this file — esphome.name and the
  # wifi_info text_sensor names below — still resolve if the board is inspected on
  # its own. friendly_name is deliberately NOT defaulted (a board-level default
  # would override the entry point's value; nothing here references it eagerly).
  device_name: an-quad
  logger_level: INFO

  # Fixed board GPIOs exposed so entry points/packages can compose devices on
  # them without hardcoding pins. The four LED channels are declared as raw LEDC
  # outputs below; the temperature-sensor and spare-header pins are left for the
  # entry point (their behaviour is application policy).
  led_pwm_frequency: "20000Hz" # quinled.info An-Quad ESPHome sample default
  temperature_sensor_pin: GPIO18 # onboard DS18B20 (unclaimed by the board)
  # Two GPIOs broken out on the An-Quad expansion header (the board's "2 GPIO
  # in/outputs available through pin headers"). Left UNCLAIMED by the board so an
  # entry point decides their use; in this repo the An-Quad is a CAN LED actuator
  # (ADR-0020/ADR-0021), so the entry point composes an external SN65HVD230 CAN
  # transceiver on them (aux_gpio_1 -> CTX as TWAI tx, aux_gpio_2 -> CRX as TWAI rx).
  # Neither is a strapping pin, so there is no boot-level constraint on the split.
  aux_gpio_1: GPIO22 # spare header GPIO — CAN tx (to transceiver CTX) in the actuator deployment
  aux_gpio_2: GPIO23 # spare header GPIO — CAN rx (from transceiver CRX) in the actuator deployment

esphome:
  name: ${device_name}
  friendly_name: ${friendly_name}
  # Repo toolchain floor (not an An-Quad hardware requirement); keeps every entry
  # point on one ESPHome baseline.
  min_version: 2026.8.0
  comment: "QuinLED-An-Quad"

# Classic ESP32 (ESP32-WROOM-32), WiFi only — no RMII Ethernet PHY on this board.
esp32:
  board: esp32dev
  framework:
    type: esp-idf

# Enable logging
logger:
  level: ${logger_level}

# Enable Home Assistant API
api:
  encryption:
    key: ${encryption_key}

# Allow Over-The-Air updates
ota:
  - platform: esphome
    password: ${ota_password}

# WiFi — the An-Quad's only network (no Ethernet PHY), so it is declared directly
# here rather than in a swappable network package.
wifi:
  ssid: !secret wifi_ssid
  password: !secret wifi_password

# # Enable AP when WiFi connection fails
# ap:
#   ssid: ${device_name} AP
#   password: !secret wifi_hotspot_pass

# captive_portal:

# The spare expansion-header GPIOs (aux_gpio_1/aux_gpio_2) are intentionally NOT claimed here —
# they are exposed as substitutions above and an entry point decides their use (AD-4). In this
# repo the An-Quad is a CAN LED actuator (ADR-0020/ADR-0021), so the entry point composes a CAN
# transceiver on those pins.

# Four LEDC PWM channels — the board's fixed, defining hardware, given stable ids
# (led_ch1..led_ch4). Entry points build light entities on top of these raw
# outputs, which by themselves impose no colour-mode policy.
output:
  - platform: ledc
    id: led_ch1
    pin: GPIO16
    frequency: ${led_pwm_frequency}
  - platform: ledc
    id: led_ch2
    pin: GPIO17
    frequency: ${led_pwm_frequency}
  - platform: ledc
    id: led_ch3
    pin:
      number: GPIO5 # strapping pin (boot log / SDIO timing); board is designed for it
      ignore_strapping_warning: true
    frequency: ${led_pwm_frequency}
  - platform: ledc
    id: led_ch4
    pin: GPIO19
    frequency: ${led_pwm_frequency}

binary_sensor:
  - platform: status
    name: "Status"

text_sensor:
  - platform: wifi_info
    ip_address:
      name: "${device_name} - IP Address"
    ssid:
      name: "${device_name} - Wi-Fi SSID"
    bssid:
      name: "${device_name} - Wi-Fi BSSID"

# Virtual buttons (no GPIO) — standard board maintenance controls.
button:
  - platform: restart
    name: "Restart"
    id: restart_button
    entity_category: config

  - platform: factory_reset
    name: "Factory Reset"
    id: reset
    entity_category: config

  - platform: safe_mode
    name: "Safe Mode"
    internal: false
    entity_category: config

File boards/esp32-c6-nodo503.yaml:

# =============================================================================
# esp32-c6-nodo503.yaml — wall-button node board hardware: ESP32-C6, one TWAI port
# =============================================================================
# Hardware: hardware/nodo503/ (rev C: ESP32-C6-WROOM-1-N8, TJA1051T/3 with VIO at 3.3 V,
# 24 V from the bus -> 5 V -> 3.3 V, six button inputs with 3.3k pull-ups on two JST PH
# connectors, Qwiic port without pull-ups). Used by the `buttons-c6` profile (ADR-0025).
#
# can0 = the bus (J1): TX GPIO23, RX GPIO22. This is the only CAN port, so it is the
# controller-facing one (node_core.yaml invariant 1).
#
# Same ADR-0005 posture as the other nodes: esp-idf watchdogs and brownout pinned, task
# watchdog panics, NO wifi:/api:/ota:/bluetooth:. Flash and logs over native USB on J5
# (not fitted; 5V, D-, D+, GND, BOOT; jumper pins 5-6 = download mode). The standalone
# Wi-Fi/Home Assistant bring-up firmware (hardware/nodo503/firmware/nodo503.yaml) stays
# valid for bench boards until the bus has been proven on this hardware.
#
# I2C (Qwiic: SDA GPIO3, SCL GPIO2) is deliberately NOT declared here: no profile
# for this board carries the sensor kit, and an unused bus is one less thing to hang.
# =============================================================================

substitutions:
  logger_level: INFO

esphome:
  min_version: 2026.8.0

esp32:
  board: esp32-c6-devkitc-1
  variant: esp32c6
  flash_size: 8MB
  framework:
    type: esp-idf
    sdkconfig_options:
      CONFIG_ESP_TASK_WDT_PANIC: y
      CONFIG_ESP_INT_WDT: y
      CONFIG_ESP_BROWNOUT_DET: y
      CONFIG_BOOTLOADER_WDT_ENABLE: y

logger:
  level: ${logger_level}
  hardware_uart: USB_SERIAL_JTAG

canbus:
  - platform: esp32_can
    id: can0
    use_extended_id: true
    # Component default TX id (CAT_STATUS base). Every send specifies an
    # explicit can_id + use_extended_id, so this is never relied on.
    can_id: 0x06000000
    tx_pin: GPIO23
    rx_pin: GPIO22
    bit_rate: 125KBPS

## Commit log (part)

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2026-06-03 chore: close epic 3 — commit story 3.3, retro, sprint-status
2026-06-03 chore: deferred work
2026-06-05 complete epic 4
2026-06-05 improve ADRs
2026-06-09 accept ADR0007
2026-06-10 docs: approve ADR-0004 and align follow-up artifacts
2026-06-11 docs: accept ADR-0008 + post-LIVE evolution artifacts
    Ratify ADR-0008 (Proposed->Accepted, acceptedDate 2026-06-11). Add the two open-item artifacts it calls for: docs/live-freeze-checklist.md (gate from section 5) and docs/reflash-campaign-runbook.md (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
2026-06-13 feat: accept ADR-0012 + hold/release button gestures
    Single gesture vocabulary (ADR-0012): replace release-time long/extra-long press with a press-phase HOLD (fires once ON >= hold_ms, default 800) and HOLD_RELEASE pair; a long press is derived central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
